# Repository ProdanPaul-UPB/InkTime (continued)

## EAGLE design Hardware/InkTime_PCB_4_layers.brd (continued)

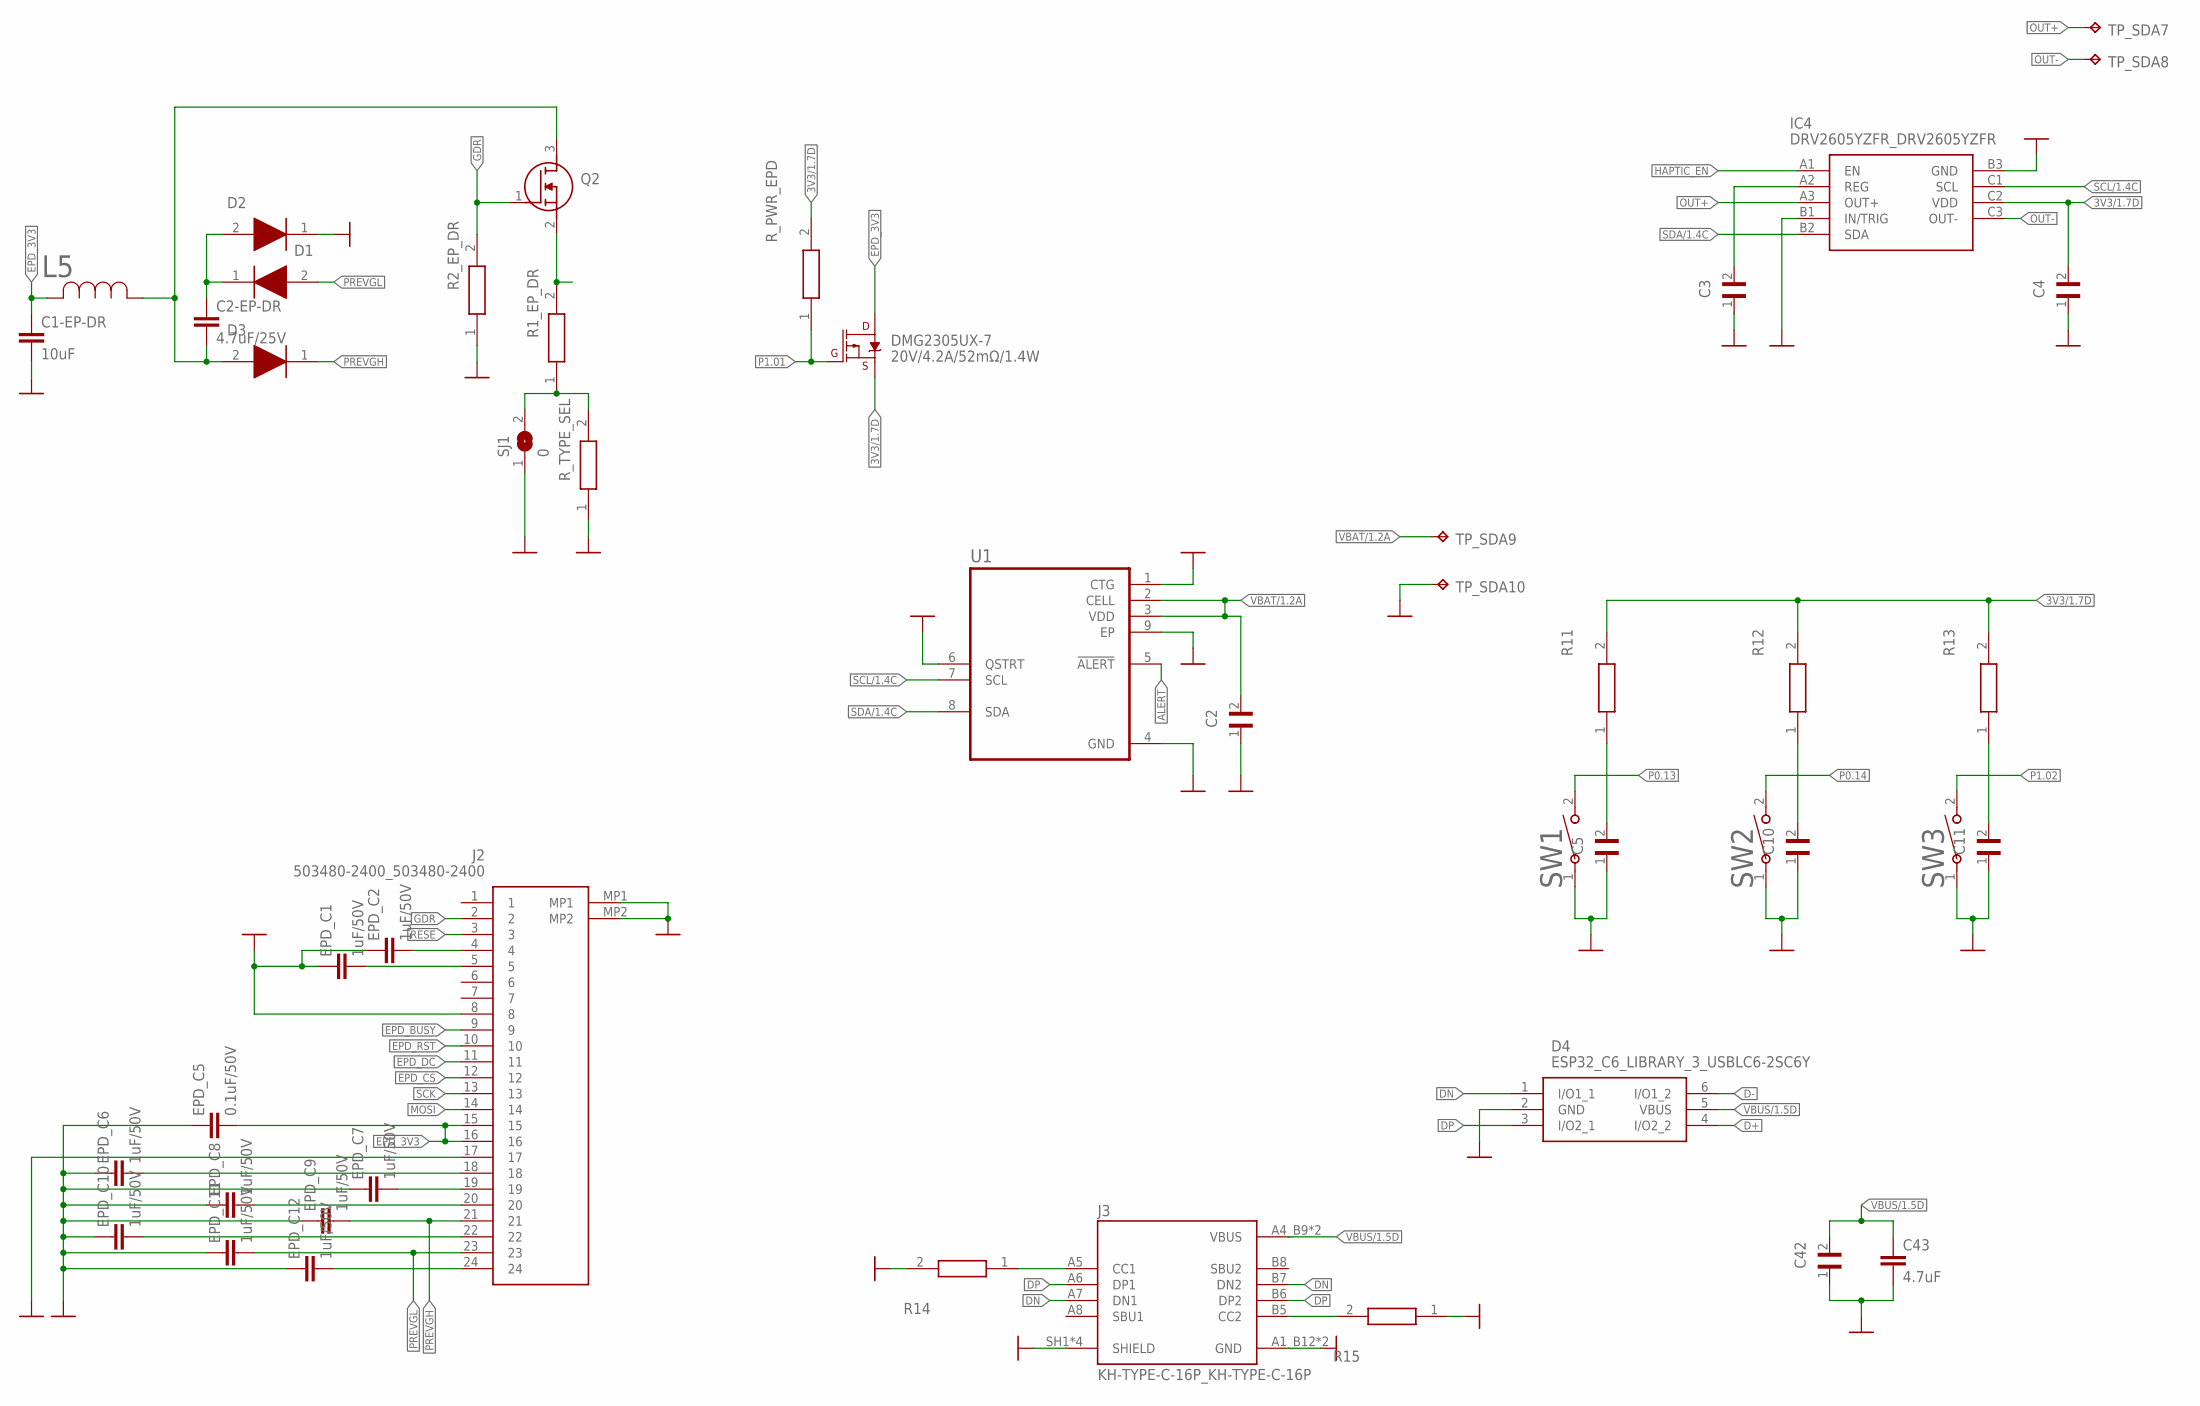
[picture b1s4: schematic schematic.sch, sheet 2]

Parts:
C1-EP-DR: 10uF; NORDIC_NRF_3_RESC0402_M
C2, C5, C10, C11, C42: GRM011R60J152KE01L_1_GRM011R60J152KE01L; GRM011R60J152KE01L_1_0201
C2-EP-DR: 4.7uF/25V; ESP32_C6_LIBRARY_1_ESP32_WROVER_EAGLE-LTSPICE_C0402
C3: 1uF; GRM011R60J152KE01L_1_0201
C4: 0.1uF; GRM011R60J152KE01L_1_0201
C43: 4.7uF; NORDIC_NRF_3_RESC0402_M
D1, D2, D3: ESP32_C6_LIBRARY_5_MBR0530; ESP32_C6_LIBRARY_5_SOD3716X135N
D4: ESP32_C6_LIBRARY_3_USBLC6-2SC6Y; ESP32_C6_LIBRARY_3_SOT95P280X145-6N
DMG2305UX-7: 20V/4.2A/52mΩ/1.4W; ESP32_C6_LIBRARY_4_ESP32_C6_LIBRARY_4_ESP32_C6_LIBRARY_4_ES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
EPD_C1, EPD_C2, EPD_C6, EPD_C7, EPD_C8, EPD_C9, EPD_C10, EPD_C11, EPD_C12: 1uF/50V; NORDIC_NRF_3_RESC0402_M
EPD_C5: 0.1uF/50V; NORDIC_NRF_3_RESC0402_M
IC4: DRV2605YZFR_DRV2605YZFR; DRV2605YZFR_BGA9C50P3X3_144X144X62
J2: 503480-2400_503480-2400; 503480-2400_5034802400
J3: KH-TYPE-C-16P_KH-TYPE-C-16P; KH-TYPE-C-16P_KINGHELM_KH-TYPE-C-16P
L5: ESP32_C6_LIBRARY_2_744043680IND_4828-WE-TPC_WRE; ESP32_C6_LIBRARY_2_IND_4828-WE-TPC_WRE
Q2: ESP32_C6_LIBRARY_6_SI1308EDL-T1-GE3; ESP32_C6_LIBRARY_6_SOT65P210X110-3N
R1_EP_DR, R2_EP_DR, R11, R12, R13, R14, R15: CPF0201D7K68C1_CPF0201D7K68C1; CPF0201D7K68C1_0201
R_PWR_EPD: CPF0201D7K68C1_CPF0201D7K68C1; CPF0201D7K68C1_0201
R_TYPE_SEL: CPF0201D7K68C1_CPF0201D7K68C1; CPF0201D7K68C1_0201
SJ1: 0; ESP32_C6_LIBRARY_7_JUMPER_SJ
SW1, SW2, SW3: 2025-10-22_07-23-44_LIBRARY_EVP-AKE31ASW_EVP-AKE3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; 2025-10-22_07-23-44_LIBRARY_SW_EVP-AKE31A_PAN
TP_SDA7, TP_SDA8, TP_SDA9, TP_SDA10: HECTOR_WATCH_1_TPTP20R; HECTOR_WATCH_1_TP20R
U1: ESP32_C6_LIBRARY_MAX17048G+T10; ESP32_C6_LIBRARY_SON50P200X200X80-9N

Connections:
ALERT: U1.5 (!ALERT); also elsewhere on the board
D+: D4.4 (I/O2_2); also elsewhere on the board
D-: D4.6 (I/O1_2); also elsewhere on the board
DN: D4.1 (I/O1_1), J3.A7 (DN1), J3.B7 (DN2)
DP: D4.3 (I/O2_1), J3.A6 (DP1), J3.B6 (DP2)
EPD_3V3: C1-EP-DR.1, DMG2305UX-7.3 (D), EPD_C5.2, J2.15, J2.16, L5.2
EPD_BUSY: J2.9; also elsewhere on the board
EPD_CS: J2.12; also elsewhere on the board
EPD_DC: J2.11; also elsewhere on the board
EPD_RST: J2.10; also elsewhere on the board
GDR: J2.2, Q2.1 (G), R2_EP_DR.2
GND: C1-EP-DR.2, C2.1, C3.1, C4.1, C5.1, C10.1, C11.1, C42.1, C43.2, D2.1 (K), D4.2 (GND), EPD_C1.1, EPD_C2.1, EPD_C5.1, EPD_C6.1, EPD_C7.1, EPD_C8.1, EPD_C9.1, EPD_C10.1, EPD_C11.1, EPD_C12.1, IC4.B1 (IN/TRIG), IC4.B3 (GND), J2.8, J2.17, J2.MP1, J2.MP2, J3.A1_B12 (GND), J3.A12_B1 (GND), J3.SH1 (SHIELD), J3.SH2 (SHIELD), J3.SH3 (SHIELD), J3.SH4 (SHIELD), R2_EP_DR.1, R14.2, R15.1, R_TYPE_SEL.1, SJ1.1, SW1.1, SW2.1, SW3.1, TP_SDA10.TP, U1.1 (CTG), U1.4 (GND), U1.6 (QSTRT), U1.9 (EP); also elsewhere on the board
HAPTIC_EN: IC4.A1 (EN); also elsewhere on the board
MOSI: J2.14; also elsewhere on the board
unnamed: C2-EP-DR.1, D1.1 (K), D2.2 (A)
unnamed: Q2.2 (S), R1_EP_DR.2
unnamed: R1_EP_DR.1, R_TYPE_SEL.2, SJ1.2
unnamed: C2-EP-DR.2, D3.2 (A), L5.1, Q2.3 (D)
unnamed: EPD_C2.2, J2.4
unnamed: EPD_C1.2, J2.5
unnamed: J3.B5 (CC2), R15.2
unnamed: EPD_C7.2, J2.19
unnamed: C5.2, R11.1
unnamed: EPD_C12.2, J2.24
unnamed: EPD_C6.2, J2.18
unnamed: EPD_C8.2, J2.20
unnamed: C10.2, R12.1
unnamed: EPD_C10.2, J2.22
unnamed: C11.2, R13.1
unnamed: J3.A5 (CC1), R14.1
unnamed: C3.2, IC4.A2 (REG)
OUT+: IC4.A3 (OUT+), TP_SDA7.TP; also elsewhere on the board
OUT-: IC4.C3 (OUT-), TP_SDA8.TP; also elsewhere on the board
P0.13: SW1.2; also elsewhere on the board
P0.14: SW2.2; also elsewhere on the board
P1.01: DMG2305UX-7.1 (G), R_PWR_EPD.1; also elsewhere on the board
P1.02: SW3.2; also elsewhere on the board
PREVGH: D3.1 (K), EPD_C9.2, J2.21
PREVGL: D1.2 (A), EPD_C11.2, J2.23
RESE: J2.3
SCK: J2.13; also elsewhere on the board

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
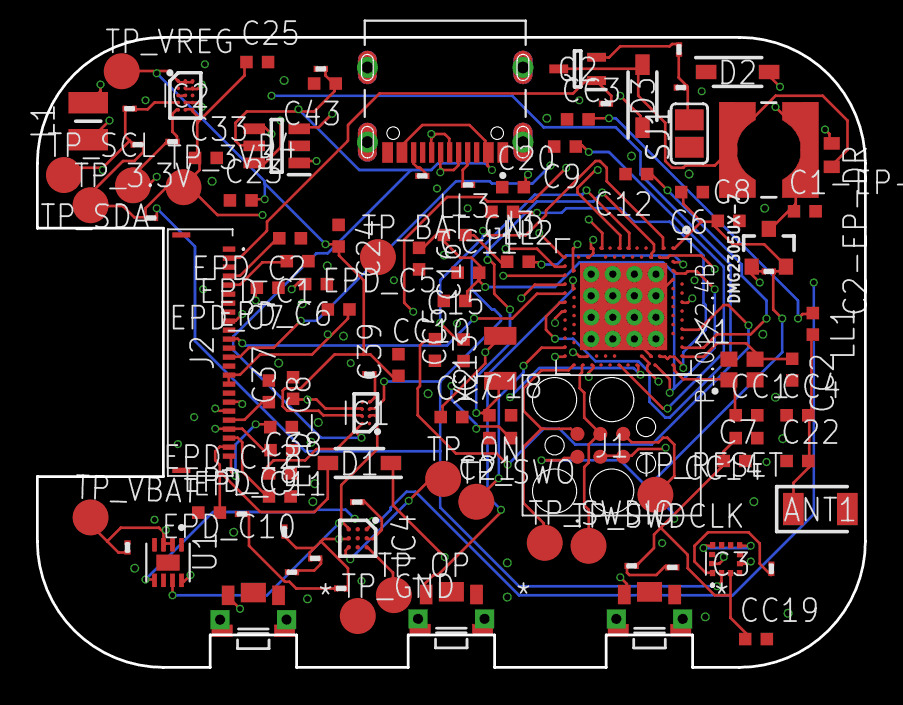
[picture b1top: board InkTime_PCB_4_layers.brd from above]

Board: 4 copper layers, 46.0 x 35.0 mm, 105 parts (0 on the bottom side), 74 nets.

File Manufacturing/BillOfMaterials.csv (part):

Qty,Value,Device,Package,Parts,Description,ARROW_PART_NUMBER,ARROW_PRICE-STOCK,AVAILABILITY,CHECK_PRICES,COPYRIGHT,DESCRIPTION,DIGI-KEY_PART_NUMBER_1,DIGI-KEY_PART_NUMBER_2,DIGI-KEY_PART_NUMBER_3,HEIGHT,JLCPCB,MANUFACTURER_NAME,MANUFACTURER_PART_NUMBER,MF,MOUSER_PART_NUMBER,MOUSER_PRICE-STOCK,MP,PACKAGE,POPULARITY,PRICE,PURCHASE-URL,SNAPEDA_LINK,SPICEMODEL,SPICEPREFIX,TP_SIGNAL_NAME
1,0,ESP32_C6_LIBRARY_7_JUMPER_SJ,ESP32_C6_LIBRARY_7_JUMPER_SJ,SJ1,"SMD solder JUMPER",,,,,,,,,,,,,,,,,,,3,,,,,,
1,0.1uF,GRM011R60J152KE01L_1_GRM011R60J152KE01L,GRM011R60J152KE01L_1_0201,C4,"Check availability",,,,,,,,,,,,,,,,,,,,,,,,,
1,0.1uF,NORDIC_NRF_3_CAPACITOR_0402_M,NORDIC_NRF_3_RESC0402_M,C23,"Generic chip capacitor",,,,,,,,,,,,,,,,,,,,,,,,,
1,0.1uF/50V,NORDIC_NRF_3_CAPACITOR_0402_M,NORDIC_NRF_3_RESC0402_M,EPD_C5,"Generic chip capacitor",,,,,,,,,,,,,,,,,,,,,,,,,
4,100nF,NORDIC_NRF_3_CAPACITOR_0402_M,NORDIC_NRF_3_RESC0402_M,"C7, C8, CC5, CC19","Generic chip capacitor",,,,,,,,,,,,,,,,,,,,,,,,,
2,100pF,NORDIC_NRF_3_CAPACITOR_0402_M,NORDIC_NRF_3_RESC0402_M,"C12, CC11","Generic chip capacitor",,,,,,,,,,,,,,,,,,,,,,,,,
1,10K,CPF0201D7K68C1_CPF0201D7K68C1,CPF0201D7K68C1_0201,R9,"7.68k 0201 Thin Film Surface Mount Fixed Resistor +/-0.5% 0.031W CPF0201D7K68C1",,,,,,,,,,,,,,,,,,,,,,,,,
3,10uF,NORDIC_NRF_3_CAPACITOR_0402_M,NORDIC_NRF_3_RESC0402_M,"C1-EP-DR, C24, C39","Generic chip capacitor",,,,,,,,,,,,,,,,,,,,,,,,,
1,10uH,NORDIC_NRF_2_INDUCTOR_0402_M,NORDIC_NRF_2_RESC0402_M,LL2,"Generic chip inductor",,,,,,,,,,,,,,,,,,,,,,,,,
4,12pF,NORDIC_NRF_3_CAPACITOR_0402_M,NORDIC_NRF_3_RESC0402_M,"C17, C18, CC1, CC2","Generic chip capacitor",,,,,,,,,,,,,,,,,,,,,,,,,
1,15uH,NORDIC_NRF_2_INDUCTOR_0402_M,NORDIC_NRF_2_RESC0402_M,LL3,"Generic chip inductor",,,,,,,,,,,,,,,,,,,,,,,,,
2,1pF,NORDIC_NRF_3_CAPACITOR_0402_M,NORDIC_NRF_3_RESC0402_M,"CC3, CC4","Generic chip capacitor",,,,,,,,,,,,,,,,,,,,,,,,,
1,1uF,GRM011R60J152KE01L_1_GRM011R60J152KE01L,GRM011R60J152KE01L_1_0201,C3,"Check availability",,,,,,,,,,,,,,,,,,,,,,,,,
3,1uF,NORDIC_NRF_3_CAPACITOR_0402_M,NORDIC_NRF_3_RESC0402_M,"C15, C37, C38","Generic chip capacitor",,,,,,,,,,,,,,,,,,,,,,,,,
9,1uF/50V,NORDIC_NRF_3_CAPACITOR_0402_M,NORDIC_NRF_3_RESC0402_M,"EPD_C1, EPD_C2, EPD_C6, EPD_C7, EPD_C8, EPD_C9, EPD_C10, EPD_C11, EPD_C12","Generic chip capacitor",,,,,,,,,,,,,,,,,,,,,,,,,
3,2025-10-22_07-23-44_LIBRARY_EVP-AKE31ASW_EVP-AKE31A_PAN,2025-10-22_07-23-44_LIBRARY_EVP-AKE31ASW_EVP-AKE31A_PAN,2025-10-22_07-23-44_LIBRARY_SW_EVP-AKE31A_PAN,"SW1, SW2, SW3",,,,,,"Copyright (C) 2025 Ultra Librarian. All rights reserved.",,P123437TR-ND,P123437CT-ND,P123437DKR-ND,,,Panasonic,EVP-AKE31A,,,,,,,,,,,,
2,22uF,NORDIC_NRF_3_CAPACITOR_0402_M,NORDIC_NRF_3_RESC0402_M,"C25, C33","Generic chip capacitor",,,,,,,,,,,,,,,,,,,,,,,,,
1,2450AT18B100E_2450AT18B100E,2450AT18B100E_2450AT18B100E,2450AT18B100E_ANTC3216X140N,ANT1,"Antennas 2.45GHz ANTENNA",2450AT18B100E,https://www.arrow.com/en/products/2450at18b100e/johanson-die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,,,,"Antennas 2.45GHz ANTENNA",,,,1.4mm,,"JOHANSON TECHNOLOGY",2450AT18B100E,,609-2450AT18B100E,https://www.mouser.co.uk/ProductDetail/Johanson-Technology/2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,,,,,,,,,
1,3.9nH,NORDIC_NRF_2_INDUCTOR_0402_M,NORDIC_NRF_2_RESC0402_M,LL1,"Generic chip inductor",,,,,,,,,,,,,,,,,,,,,,,,,
1,32.768KHz,NORDIC_NRF_1_XTAL_32KHZ,NORDIC_NRF_1_XTAL_3215_N,X2,,,,,,,,,,,,,,,,,,,,,,,,,,
1,32MHz,NORDIC_NRF_XTAL_32MHZ,NORDIC_NRF_BT-XTAL_2016_N,X1,,,,,,,,,,,,,,,,,,,,,,,,,,
5,4.7uF,NORDIC_NRF_3_CAPACITOR_0402_M,NORDIC_NRF_3_RESC0402_M,"C6, C20, C21, C43, CC14","Generic chip capacitor",,,,,,,,,,,,,,,,,,,,,,,,,
1,4.7uF/25V,ESP32_C6_LIBRARY_1_ESP32_WROVER_EAGLE-LTSPICE_CC0402,ESP32_C6_LIBRARY_1_ESP32_WROVER_EAGLE-LTSPICE_C0402,C2-EP-DR,"CAPACITOR, European symbol",,,,,,,,,,,,,,,,,,,,,,,NONE,C,
1,47nF,NORDIC_NRF_3_CAPACITOR_0402_M,NORDIC_NRF_3_RESC0402_M,C16,"Generic chip capacitor",,,,,,,,,,,,,,,,,,,,,,,,,
1,503480-2400_503480-2400,503480-2400_503480-2400,503480-2400_5034802400,J2,"FFC & FPC Connectors 0.5mm FPC RA SMT Dual Contact 24Ckt",,,,,,"FFC & FPC Connectors 0.5mm FPC RA SMT Dual Contact 24Ckt",,,,1.87mm,,Molex,503480-2400,,538-503480-2400,https://www.mouser.co.uk/ProductDetail/Molex/503480-2400?qs=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,,,,,,,,,
1,820pF,NORDIC_NRF_3_CAPACITOR_0402_M,NORDIC_NRF_3_RESC0402_M,C9,"Generic chip capacitor",,,,,,,,,,,,,,,,,,,,,,,,,
1,BMA423_BMA423,BMA423_BMA423,BMA423_BMA423,IC3,"Accelerometers Triaxial low-g 12bit Acceleration Sensor",BMA423,https://www.arrow.com/en/products/bma423/bosch,,,,"Accelerometers Triaxial low-g 12bit Acceleration Sensor",,,,1mm,,BOSCH,BMA423,,262-BMA423,https://www.mouser.co.uk/ProductDetail/Bosch-Sensortec/BMA42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,,,,,,,,,
1,BQ25180YBGR_BQ25180YBGR,BQ25180YBGR_BQ25180YBGR,BQ25180YBGR_BGA8C40P2X4_100X155X50,IC1,"Charger IC Lithium Ion/Polymer, Lithium Iron Phosphate 8-DSBGA (1.6x1.1)",BQ25180YBGR,https://www.arrow.com/en/products/bq25180ybgr/texas-instrume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,,,,"Charger IC Lithium Ion/Polymer"," Lithium Iron Phosphate 8-DSBGA (1.6x1.1)",,,,0.5mm,,"Texas Instruments",BQ25180YBGR,,595-BQ25180YBGR,https://www.mouser.co.uk/ProductDetail/Texas-Instruments/BQ2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,,,,,,,,
10,CPF0201D7K68C1_CPF0201D7K68C1,CPF0201D7K68C1_CPF0201D7K68C1,CPF0201D7K68C1_0201,"R2, R3, R4, R5, R8, R11, R12, R13, R14, R15","7.68k 0201 Thin Film Surface Mount Fixed Resistor +/-0.5% 0.031W CPF0201D7K68C1",,,,,,,,,,,,,,,,,,,,,,,,,
1,DRV2605YZFR_DRV2605YZFR,DRV2605YZFR_DRV2605YZFR,DRV2605YZFR_BGA9C50P3X3_144X144X62,IC4,"Haptic Driver for ERM/LRA with Built-In Library and Smart Loop Architecture",DRV2605YZFR,https://www.arrow.com/en/products/drv2605yzfr/texas-instrume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,,,,"Haptic Driver for ERM/LRA with Built-In Library and Smart Loop Architecture",,,,0.625mm,,"Texas Instruments",DRV2605YZFR,,,,,,,,,,,,
1,ESP32_C6_LIBRARY_3_USBLC6-2SC6Y,ESP32_C6_LIBRARY_3_USBLC6-2SC6Y,ESP32_C6_LIBRARY_3_SOT95P280X145-6N,D4,"Low Cap. ESD Protection Auto SOT-23-6 STMicroelectronics USBLC6-2SC6Y, Dual Uni-Directional TVS Diode Array, 6-Pin SOT-23",,,"In Stock",https://www.snapeda.com/parts/USBLC6-2SC6Y/STMicroelectronic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,," 17V Clamp 5A (8/20µs) Ipp Tvs Diode Surface Mount SOT-23-6 ",,,,,,,,STMicroelectronics,,,USBLC6-2SC6Y,"SOT-23-6 STMicroelectronics",,None,,https://www.snapeda.com/parts/USBLC6-2SC6Y/STMicroelectronic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,,,
3,ESP32_C6_LIBRARY_5_MBR0530,ESP32_C6_LIBRARY_5_MBR0530,ESP32_C6_LIBRARY_5_SOD3716X135N,"D1, D2, D3","ON SEMICONDUCTOR - MBR0530 - DIODE, SCHOTTKY, 0.5A, 30V, SOD-123",,,"In Stock",https://www.snapeda.com/parts/MBR0530/Onsemi/view-part/?ref=eda,," Diode Schottky 30 V 500mA Surface Mount SOD-123 ",,,,,,,,"ON Semiconductor",,,MBR0530,"SOD-123-2 ON Semiconductor",,None,"https://www.snapeda.com/api/url_track_click_mouser/?unipart_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 Semiconductor&part_name=MBR0530&search_term=None",https://www.snapeda.com/parts/MBR0530/Onsemi/view-part/?ref=snap,,,
1,ESP32_C6_LIBRARY_6_SI1308EDL-T1-GE3,ESP32_C6_LIBRARY_6_SI1308EDL-T1-GE3,ESP32_C6_LIBRARY_6_SOT65P210X110-3N,Q2,"MOSFET N-Ch 30V 1.5A TrenchFET SC70 Vishay Si1308EDL-T1-GE3 N-channel MOSFET Transistor, 1.5 A, 30 V, 3-Pin SC-70",,,"In Stock",https://www.snapeda.com/parts/SI1308EDL-T1-GE3/Vishay+Silico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,," Si1308EDL-T1-GE3 N-channel MOSFET Transistor"," 1.5 A"," 30 V"," 3-Pin SC-70 | Siliconix / Vishay SI1308EDL-T1-GE3 ",,,,,,,,"Vishay Siliconix",,,SI1308EDL-T1-GE3,"SOT-323 Vishay Semiconductor",,None,"https://www.snapeda.com/api/url_track_click_mouser/?unipart_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 Siliconix&part_name=SI1308EDL-T1-GE3&search_term=None",https://www.snapeda.com/parts/SI1308EDL-T1-GE3/Vishay+Silico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
1,ESP32_C6_LIBRARY_MAX17048G+T10,ESP32_C6_LIBRARY_MAX17048G+T10,ESP32_C6_LIBRARY_SON50P200X200X80-9N,U1,"Check availability",,,"In Stock",https://www.snapeda.com/parts/MAX17048G+T10/Analog+Devices/v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,," 3µA 1-Cell/2-Cell Fuel Gauge with ModelGauge ",,,,,,,,"Analog Devices",,,MAX17048G+T10,"TDFN-8 Maxim",,None,"https://www.snapeda.com/api/url_track_click_mouser/?unipart_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 Devices&part_name=MAX17048G+T10&search_term=None",https://www.snapeda.com/parts/MAX17048G+T10/Analog+Devices/v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,,,
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
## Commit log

2026-04-06 wireframe
2026-04-06 added schematic
2026-04-06 added pcb
2026-04-09 added missing project files
2026-04-09 added pics
2026-04-18 Added GND value to GND objects
2026-04-18 redenumire TP
2026-04-18 added pcb version with correct copper dimensions and board thickness
2026-04-18 added drill file to gerberfiles
2026-04-18 added 4 layer pcb variant and fixed schematic broken connections
